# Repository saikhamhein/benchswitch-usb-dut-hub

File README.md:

# BenchSwitch USB DUT Hub

A four-port USB 2.0 DUT hub for embedded firmware development and automated hardware testing.

BenchSwitch was born from a practical need in agentic firmware development: let the development workflow power-cycle a device instead of waiting for someone to unplug it. The design combines a USB2514B hub controller with individually switched downstream power, targeting host control through tools such as `uhubctl`.

**Prototype: hardware testing is pending.** See the [build guide](doc/BUILD.md), [design constraints](doc/DESIGN_CONSTRAINTS.md) and [bring-up checklist](doc/BRINGUP.md) before building or powering a board.

## Hardware

- Four USB-A DUT ports and one USB-B upstream connection
- Per-port CH217A power switching and overcurrent signalling
- Regulated 12–24 V DC input with buck conversion
- Design targets: 1 A per port, 2 A shared DUT current
- 95 × 80 mm, four-layer PCB
- KiCad 10.0.6 sources; 131 fitted components across 41 catalog groups

## Build

Open [BenchSwitch_USB_DUT_Hub.kicad_pro](PCB/BenchSwitch_USB_DUT_Hub.kicad_pro) in KiCad 10.0.6.

- [Schematic](doc/PCB_Schematic_R5_LCSC.pdf) and [assembly drawing](doc/PCB_Assembly_R5_LCSC.pdf)
- [Gerber ZIP](manufacturing/R5_LCSC/DIN_USB_Hub_A8_R5_LCSC_Gerber.zip)
- [Exact component BOM](manufacturing/R5_LCSC/assembly/BOM_exact_per_reference.csv) and [per-board procurement list](manufacturing/R5_LCSC/LCSC_PROCUREMENT_PER_BOARD.csv)

With Python 3.9+, verify the release files or export to a new directory:

```sh
python manufacturing/tools/verify_release.py
python manufacturing/tools/export_manufacturing.py --output build/manufacturing
```

## Files

- `PCB/`: native design, symbols, footprints and models
- `manufacturing/`: fabrication files, BOM and build tools
- `doc/`: drawings, assembly guidance and test procedures

[CAD verification](doc/VERIFICATION.json) · [Third-party notices and optional model downloads](doc/THIRD_PARTY.md)

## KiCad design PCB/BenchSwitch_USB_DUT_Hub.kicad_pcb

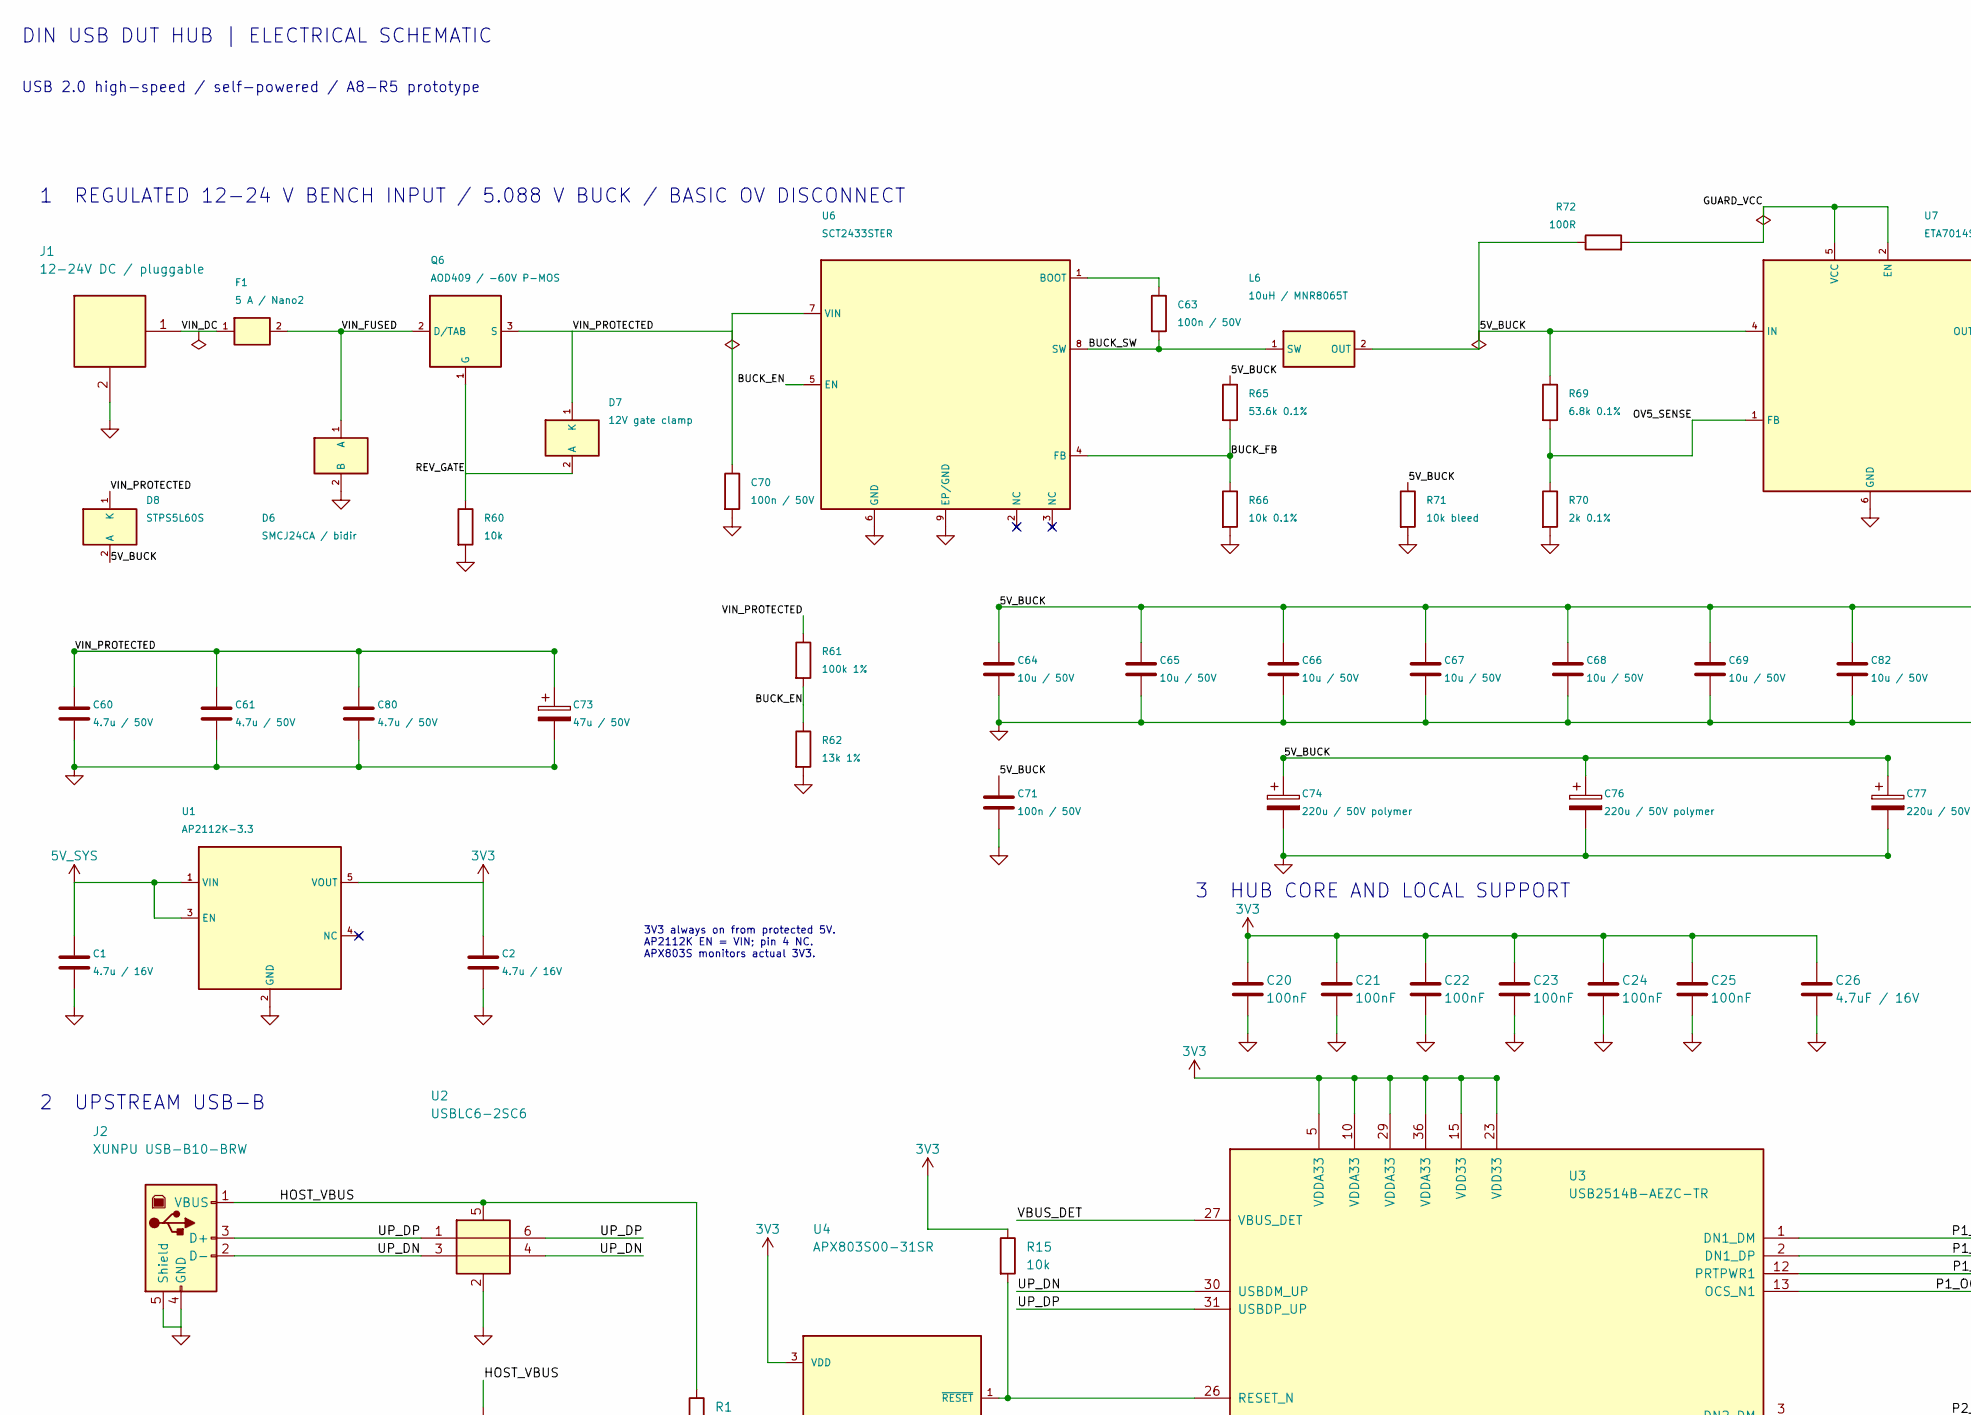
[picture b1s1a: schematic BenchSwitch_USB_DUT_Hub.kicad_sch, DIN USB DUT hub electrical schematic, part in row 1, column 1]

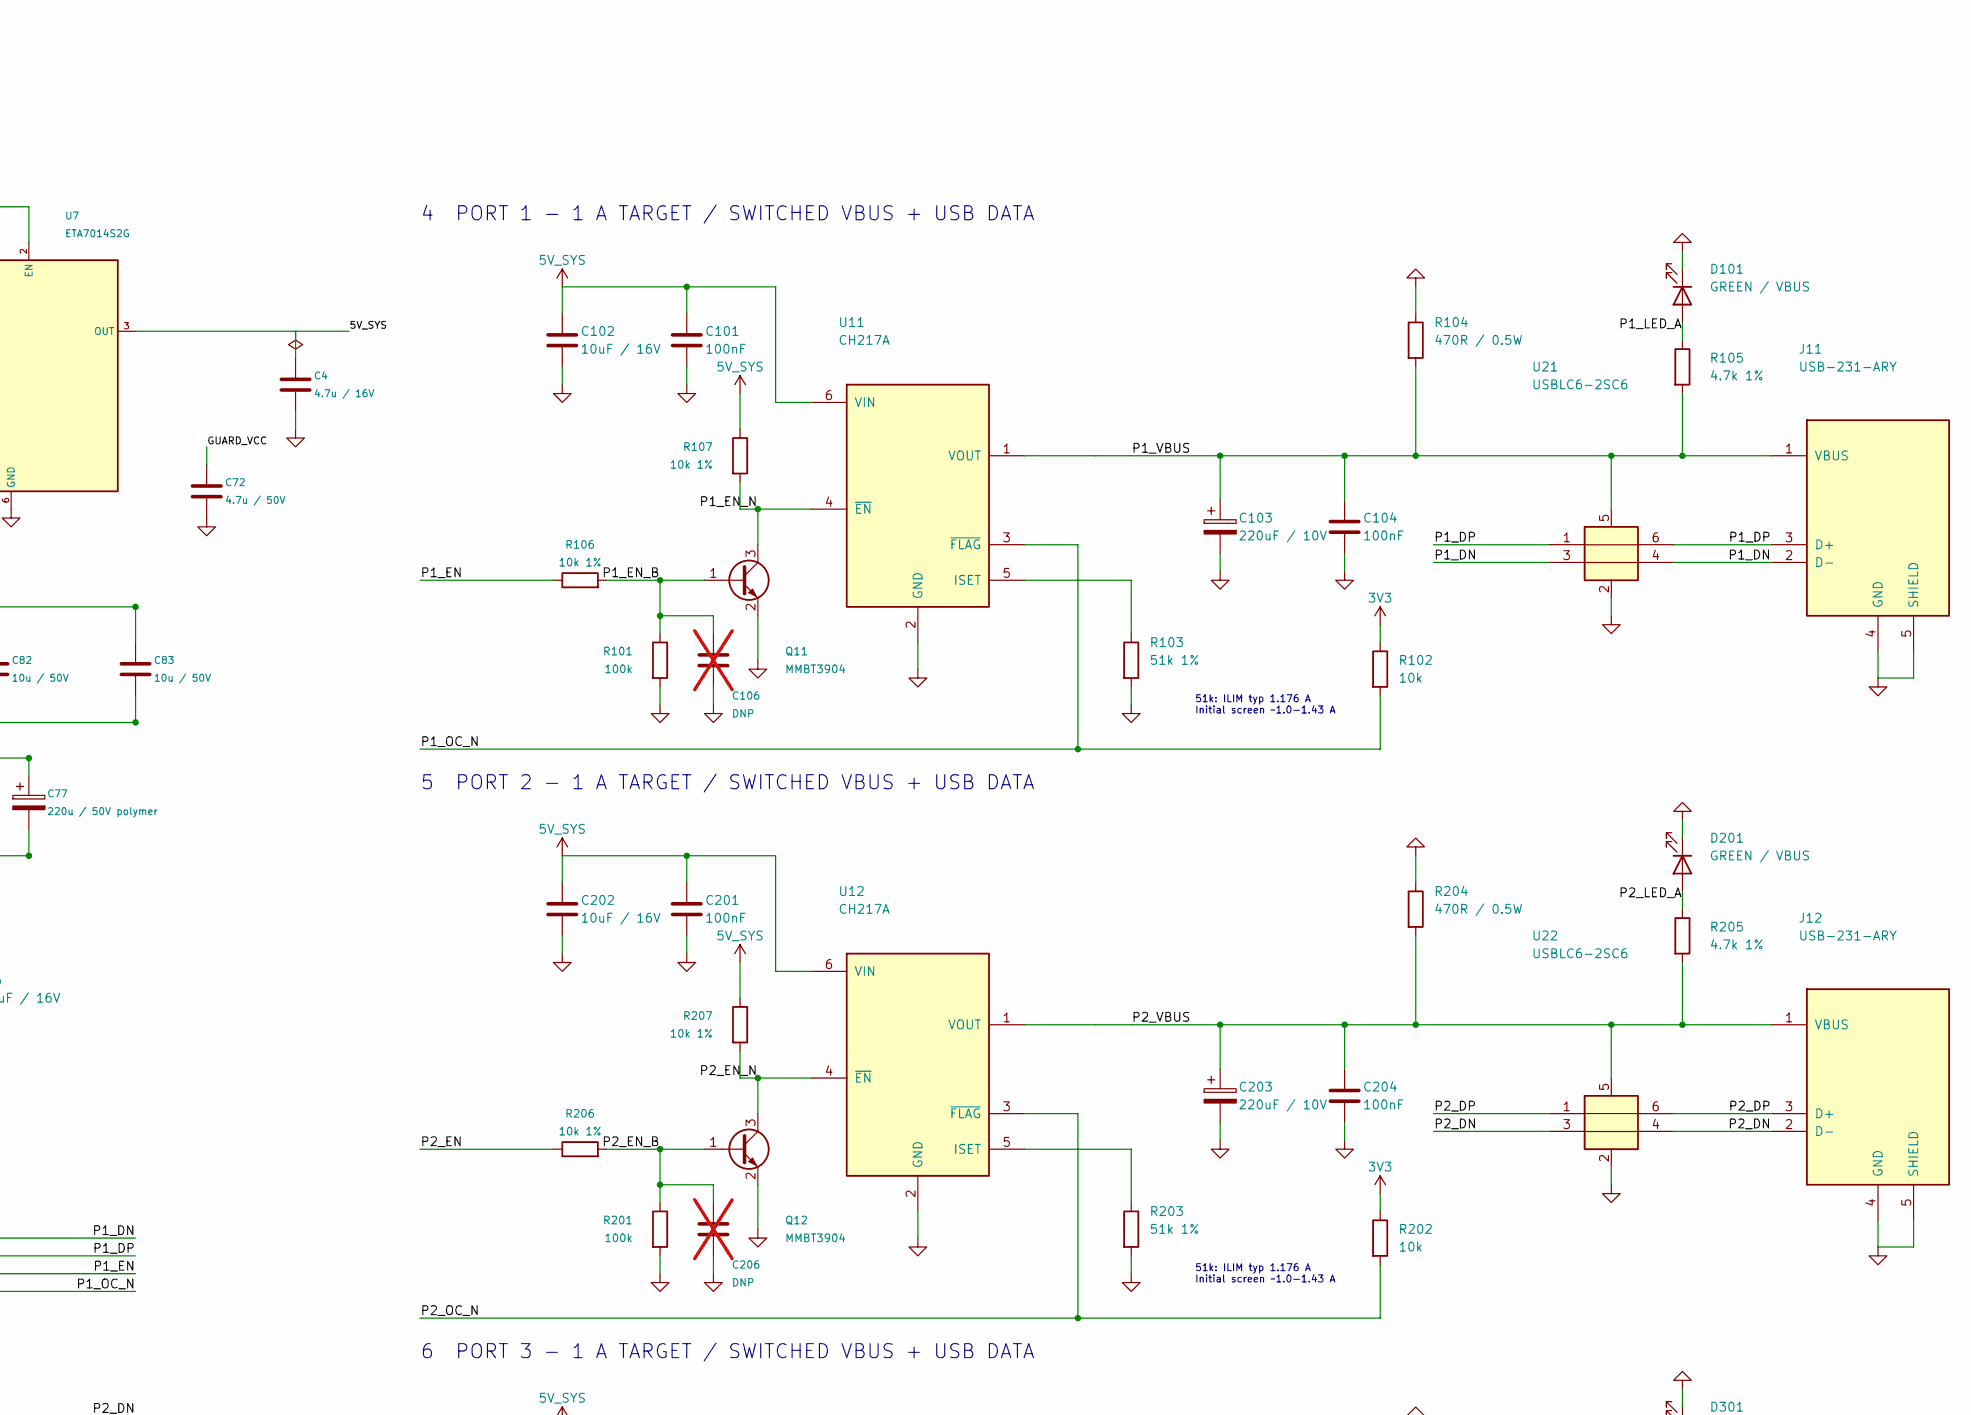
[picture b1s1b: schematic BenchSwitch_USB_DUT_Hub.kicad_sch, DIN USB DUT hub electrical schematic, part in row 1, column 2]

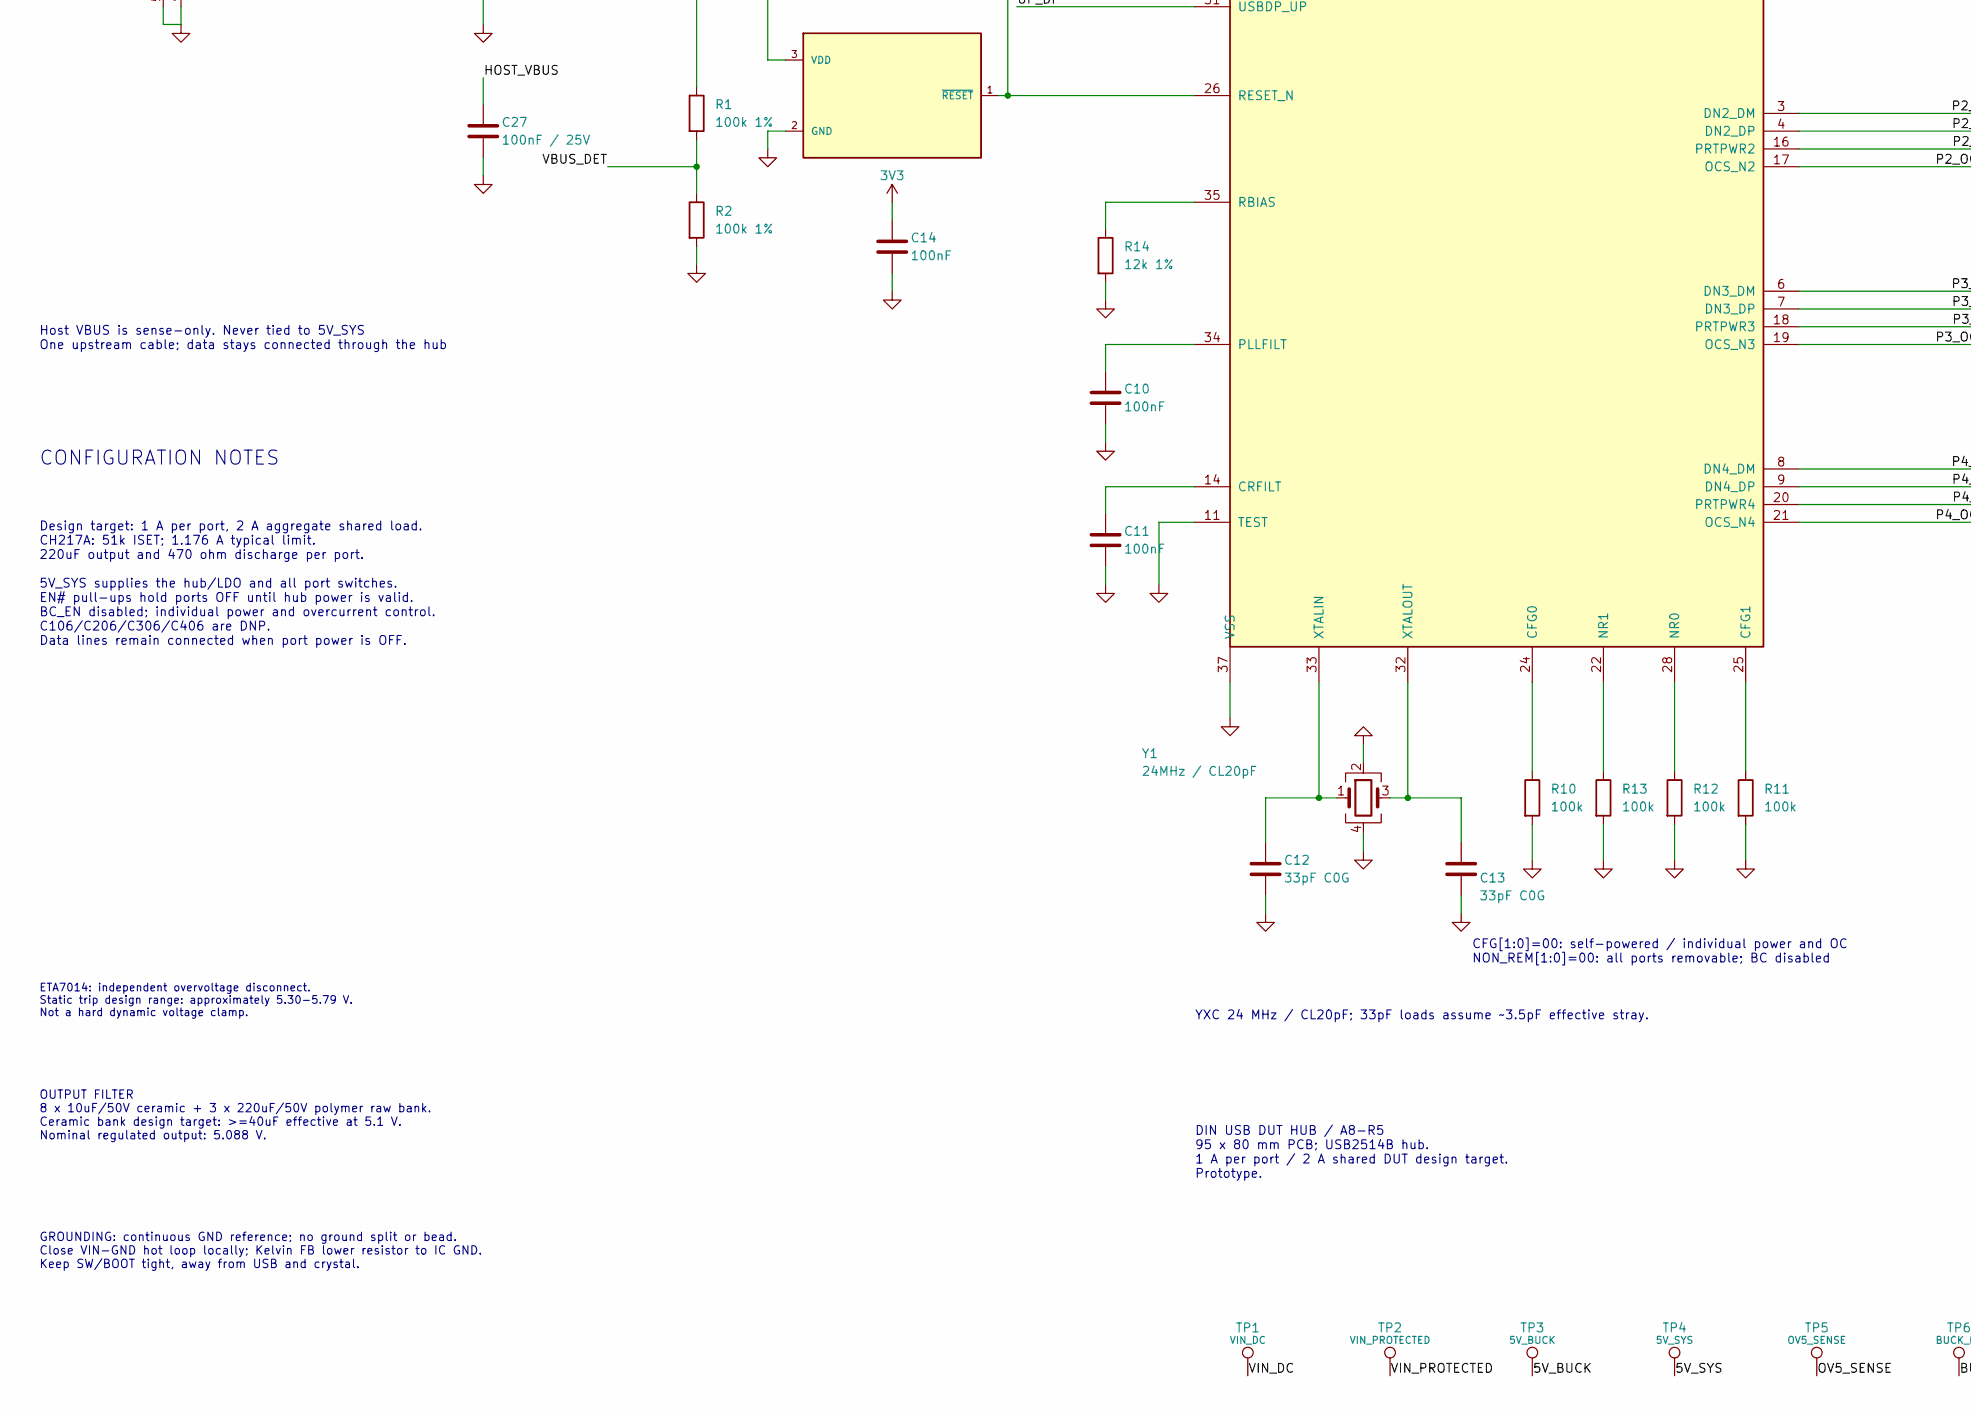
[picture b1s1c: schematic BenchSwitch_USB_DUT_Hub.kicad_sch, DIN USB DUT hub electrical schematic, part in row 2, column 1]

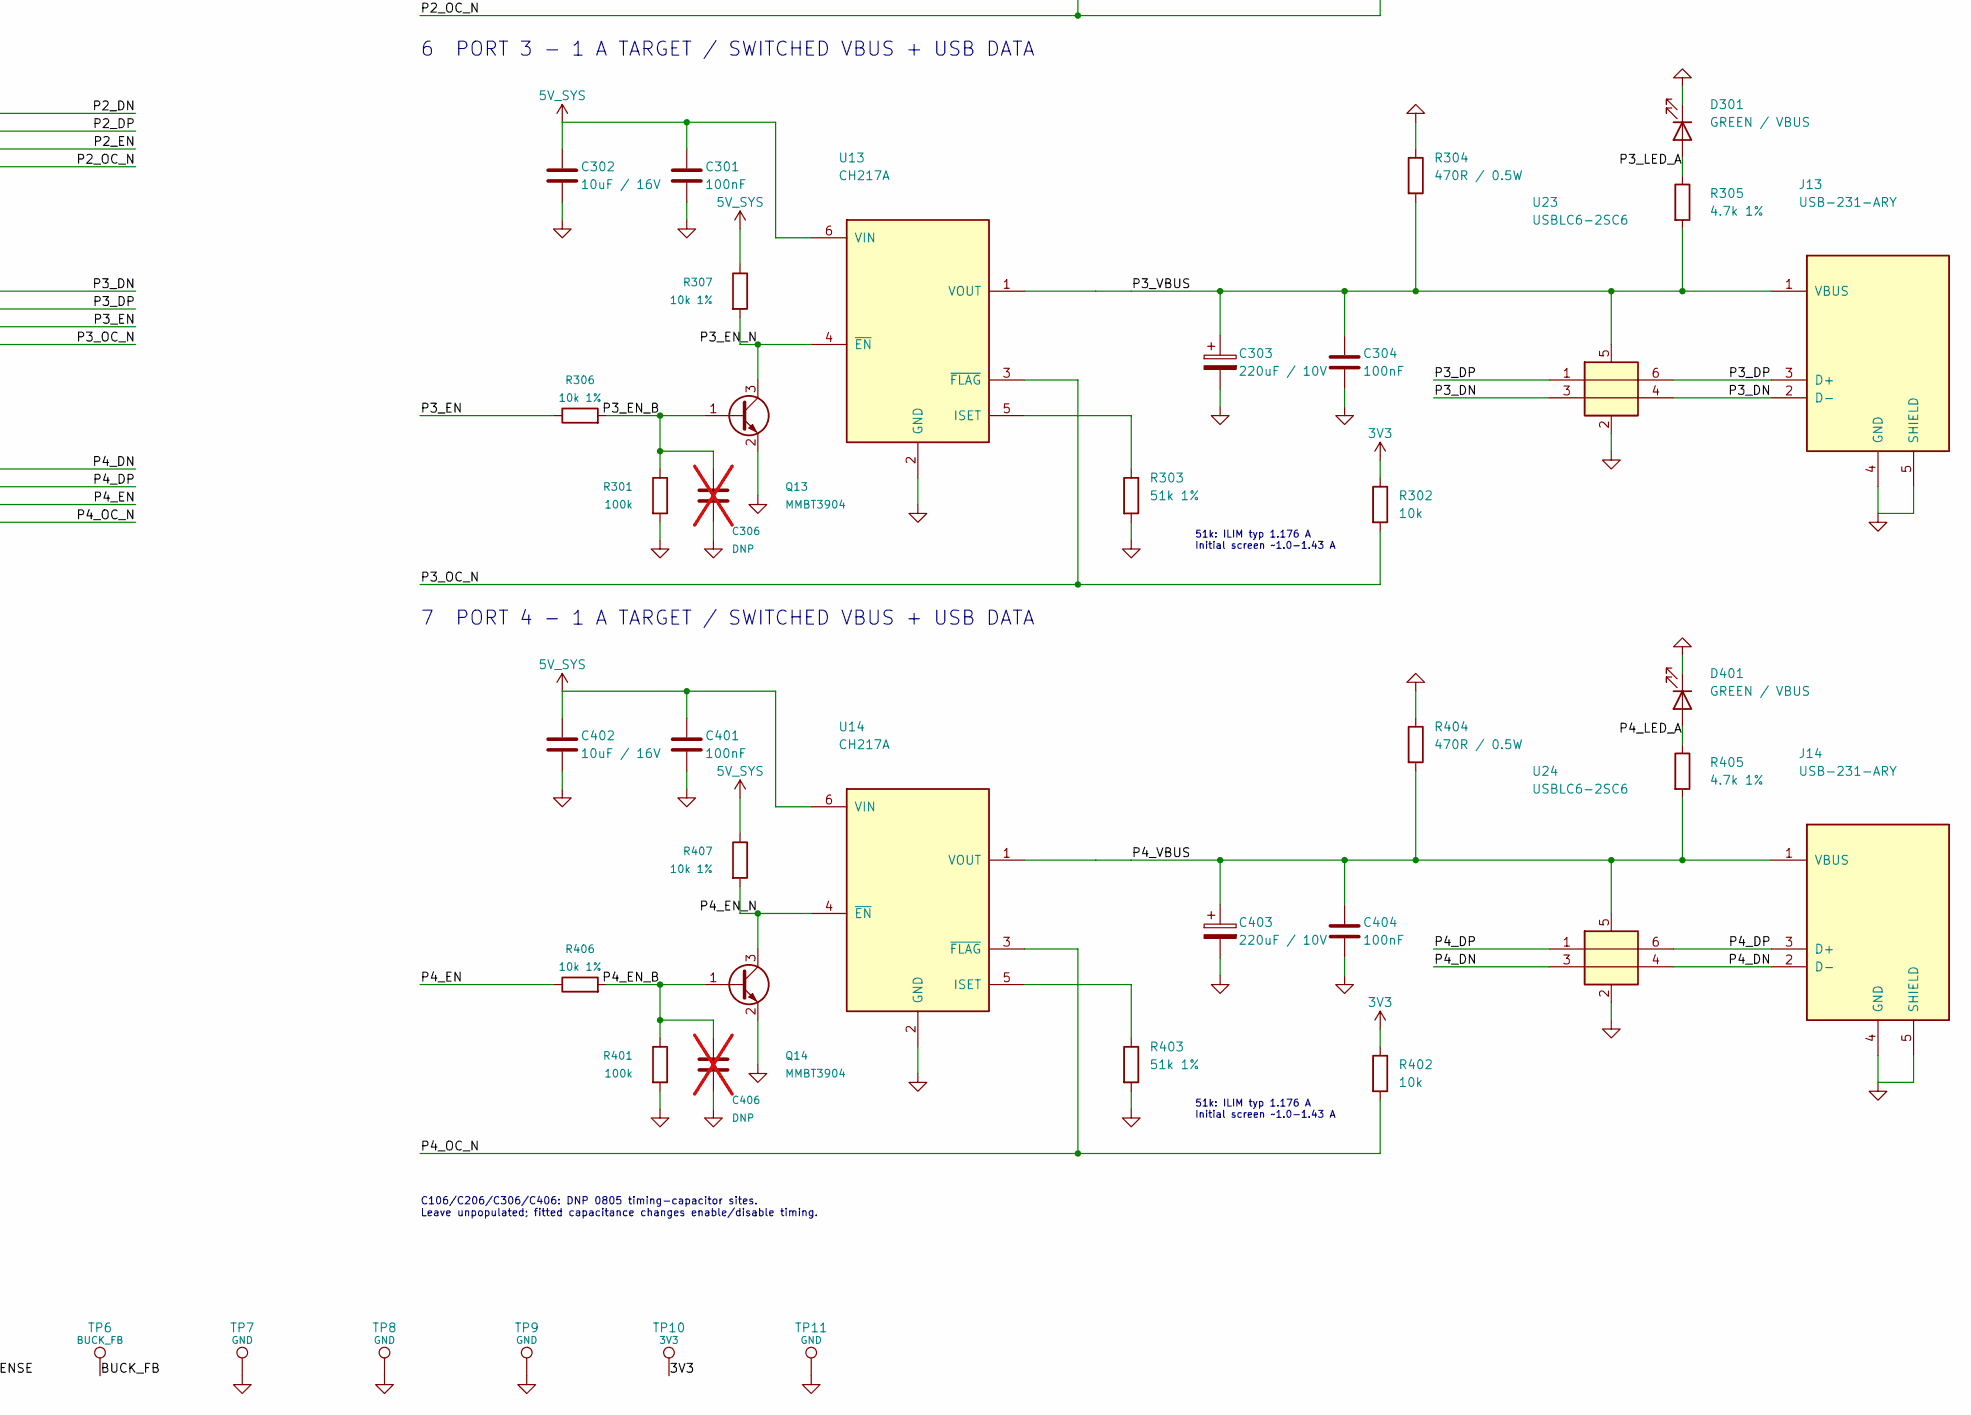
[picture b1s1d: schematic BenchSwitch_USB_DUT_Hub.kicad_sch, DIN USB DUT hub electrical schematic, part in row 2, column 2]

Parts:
C1, C2, C4: 4.7u / 16V; C_0805_2012Metric; MPN 0805B475K160NT; LCSC C880382
C10, C11, C14, C21, C22, C23, C24, C25, C101, C104, C201, C204, C301, C304, C401, C404: 100nF; C_0603_1608Metric; Tolerance 10%; MPN CC0603KRX7R9BB104; LCSC C14663
C12, C13: 33pF C0G; C_0603_1608Metric; MPN CL10C330JB8NNNC; LCSC C1663
C20: 100nF; C_0402_1005Metric; Tolerance 10%; MPN CC0402KRX7R8BB104; LCSC C105883
C26: 4.7uF / 16V; C_0805_2012Metric; MPN 0805B475K160NT; LCSC C880382
C27: 100nF / 25V; C_0402_1005Metric; Tolerance 10%; MPN CC0402KRX7R8BB104; LCSC C105883
C60, C61, C72, C80: 4.7u / 50V; C_1206_3216Metric; MPN 1206B475K500NT; LCSC C29823
C63, C70: 100n / 50V; R_0603_1608Metric; MPN CC0603KRX7R9BB104; LCSC C14663
C64, C65, C66, C67, C68, C69, C82, C83: 10u / 50V; Samsung_CL31_1206; MPN CL31B106KBHNFNE; LCSC C913957
C71: 100n / 50V; C_0603_1608Metric; MPN CC0603KRX7R9BB104; LCSC C14663
C73: 47u / 50V; CP_Radial_D6.3mm_P2.50mm; MPN SPZ1HM470E08O00RAXXX; LCSC C122243
C74, C76, C77: 220u / 50V polymer; CP_Radial_D10.0mm_P5.00mm; MPN SPZ1HM221G12O00RAXXX; LCSC C2691846
C102, C202, C302, C402: 10uF / 16V; C_0805_2012Metric; Tolerance 10%; MPN CC0805KKX7R7BB106; LCSC C326595
C103, C203, C303, C403: 220uF / 10V; CP_Radial_D6.3mm_P2.50mm; Tolerance 20%; MPN ERS1AM221E11OT; LCSC C106640
C106, C206, C306, C406: DNP; C_0805_2012Metric; not fitted
D6: SMCJ24CA / bidir; D_SMC; MPN SMCJ24CA-13-F; LCSC C135155
D7: 12V gate clamp; D_SOD-123F; MPN BZT52H-C12,115; LCSC C282531
D8: STPS5L60S; D_SMC; MPN STPS5L60S; LCSC C140620
D101, D201, D301, D401: GREEN / VBUS; LED_LiteOn_LTST-S270KGKT_SideView; MPN LTST-S270KGKT; LCSC C125113
F1: 5 A / Nano2; Fuse_Littelfuse-NANO2-451_453; MPN 0451005.MRL; LCSC C48467
J1: 12-24V DC / pluggable; Phoenix_MSTBA_1757242_2pos_P5.08; MPN 1757242; LCSC C90074
J2: XUNPU USB-B10-BRW; XUNPU_USB_B10_BRW; MPN USB-B10-BRW; LCSC C720549
J11, J12, J13, J14: USB-231-ARY; XUNPU_USB_231_ARY; MPN USB-231-ARY; LCSC C720525
L6: 10uH / MNR8065T; Sunlord_SWPA8065S; MPN MNR8065T100MT; LCSC C18222125
Q6: AOD409 / -60V P-MOS; AOS_AOD409_TO252; MPN AOD409; LCSC C36220
Q11, Q12, Q13, Q14: MMBT3904; SOT-23; MPN MMBT3904LT1G; LCSC C81464
R1, R2: 100k 1%; R_0603_1608Metric; Tolerance 1%; MPN 0603WAF1003T5E; LCSC C25803
R10, R11, R12, R13, R101, R201, R301, R401: 100k; R_0603_1608Metric; Tolerance 1%; MPN 0603WAF1003T5E; LCSC C25803
R14: 12k 1%; R_0603_1608Metric; Tolerance 1%; MPN 0603WAF1202T5E; LCSC C22790
R15, R102, R202, R302, R402: 10k; R_0603_1608Metric; Tolerance 1%; MPN RC0603FR-0710KL; LCSC C98220
R60: 10k; R_0603_1608Metric; MPN RC0603FR-0710KL; LCSC C98220
R61: 100k 1%; R_0603_1608Metric; MPN 0603WAF1003T5E; LCSC C25803
R62: 13k 1%; R_0603_1608Metric; MPN 0603WAF1302T5E; LCSC C22797
R65: 53.6k 0.1%; R_0603_1608Metric; MPN ERA-3AEB5362V; LCSC C2074540
R66: 10k 0.1%; R_0603_1608Metric; MPN RT0603BRD0710KL; LCSC C95204
R69: 6.8k 0.1%; R_0603_1608Metric; MPN RT0603BRD076K8L; LCSC C861539
R70: 2k 0.1%; R_0603_1608Metric; MPN PTFR0603B2K00P9; LCSC C328425
R71: 10k bleed; R_0603_1608Metric; MPN RC0603FR-0710KL; LCSC C98220
R72: 100R; R_0603_1608Metric; MPN 0603WAF1000T5E; LCSC C22775
R103, R203, R303, R403: 51k 1%; R_0603_1608Metric; MPN 0603WAF5102T5E; LCSC C23196
R104, R204, R304, R404: 470R / 0.5W; R_0805_2012Metric; Tolerance 1%; MPN ERJ-P06F4700V; LCSC C441978
R105, R205, R305, R405: 4.7k 1%; R_0603_1608Metric; MPN 0603WAF4701T5E; LCSC C23162
R106, R107, R206, R207, R306, R307, R406, R407: 10k 1%; R_0603_1608Metric; Tolerance 1%; MPN RC0603FR-0710KL; LCSC C98220
TP1: VIN_DC; Probe_1.0mm
TP2: VIN_PROTECTED; Probe_1.0mm
TP3: 5V_BUCK; Probe_1.0mm
TP4: 5V_SYS; Probe_1.0mm
TP5: OV5_SENSE; Probe_1.0mm
TP6: BUCK_FB; Probe_0.4mm
TP7, TP8, TP9, TP11: GND; Probe_1.0mm
TP10: 3V3; Probe_1.0mm
U1: AP2112K-3.3; SOT-23-5; MPN AP2112K-3.3TRG1; LCSC C51118
U2, U21, U22, U23, U24: USBLC6-2SC6; SOT-23-6; MPN USBLC6-2SC6; LCSC C7519
U3: USB2514B-AEZC-TR; QFN-36-1EP_6x6mm_P0.5mm_EP3.7x3.7mm; MPN USB2514B-AEZC-TR; LCSC C16251
U4: APX803S00-31SR; Diodes_APX803S_SR_SOT23; MPN APX803S00-31SR-7; LCSC C2067620
U6: SCT2433STER; SCT2433_ESOP8; MPN SCT2433STER; LCSC C509399
U7: ETA7014S2G; SOT-23-6; MPN ETA7014S2G; LCSC C7465500
U11, U12, U13, U14: CH217A; SOT-23-6; MPN CH217A; LCSC C54973763
Y1: 24MHz / CL20pF; YXC_YSX531SL_5032; Tolerance See exact manufacturer grade; MPN XL1EL89CSI-111YLC-24M; LCSC C18214302

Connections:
3V3: C2.1, C14.1, C20.1, C21.1, C22.1, C23.1, C24.1, C25.1, C26.1, R15.1, R102.1, R202.1, R302.1, R402.1, TP10.1, U1.5 (VOUT), U3.5 (VDDA33), U3.10 (VDDA33), U3.15 (VDD33), U3.23 (VDD33), U3.29 (VDDA33), U3.36 (VDDA33), U4.3 (VDD)
5V_SYS: C1.1, C4.1, C101.1, C102.1, C201.1, C202.1, C301.1, C302.1, C401.1, C402.1, R107.1, R207.1, R307.1, R407.1, TP4.1, U1.1 (VIN), U1.3 (EN), U7.3 (OUT), U11.6 (VIN), U12.6 (VIN), U13.6 (VIN), U14.6 (VIN)
/5V_BUCK: C64.1, C65.1, C66.1, C67.1, C68.1, C69.1, C71.1, C74.1, C76.1, C77.1, C82.1, C83.1, D8.2 (A), L6.2 (OUT), R65.1, R69.1, R71.1, R72.1, TP3.1, U7.4 (IN)
/BUCK_EN: R61.2, R62.1, U6.5 (EN)
/BUCK_FB: R65.2, R66.1, TP6.1, U6.4 (FB)
/BUCK_SW: C63.2, L6.1 (SW), U6.8 (SW)
/GUARD_VCC: C72.1, R72.2, U7.2 (EN), U7.5 (VCC)
/HOST_VBUS: C27.1, J2.1 (VBUS), R1.1, U2.5 (VBUS)
/OV5_SENSE: R69.2, R70.1, TP5.1, U7.1 (FB)
/P1_DN: J11.2 (D-), U3.1 (DN1_DM), U21.3 (I/O2), U21.4 (I/O2)
/P1_DP: J11.3 (D+), U3.2 (DN1_DP), U21.1 (I/O1), U21.6 (I/O1)
/P1_EN: R106.1, U3.12 (PRTPWR1)
/P1_EN_B: C106.1, Q11.1 (B), R101.1, R106.2
/P1_EN_N: Q11.3 (C), R107.2, U11.4 (~EN)
/P1_LED_A: D101.2 (A), R105.1
/P1_OC_N: R102.2, U3.13 (OCS_N1), U11.3 (~FLAG)
/P1_VBUS: C103.1, C104.1, J11.1 (VBUS), R104.2, R105.2, U11.1 (VOUT), U21.5 (VBUS)
/P2_DN: J12.2 (D-), U3.3 (DN2_DM), U22.3 (I/O2), U22.4 (I/O2)
/P2_DP: J12.3 (D+), U3.4 (DN2_DP), U22.1 (I/O1), U22.6 (I/O1)
/P2_EN: R206.1, U3.16 (PRTPWR2)
/P2_EN_B: C206.1, Q12.1 (B), R201.1, R206.2
/P2_EN_N: Q12.3 (C), R207.2, U12.4 (~EN)
/P2_LED_A: D201.2 (A), R205.1
/P2_OC_N: R202.2, U3.17 (OCS_N2), U12.3 (~FLAG)
/P2_VBUS: C203.1, C204.1, J12.1 (VBUS), R204.2, R205.2, U12.1 (VOUT), U22.5 (VBUS)
/P3_DN: J13.2 (D-), U3.6 (DN3_DM), U23.3 (I/O2), U23.4 (I/O2)
/P3_DP: J13.3 (D+), U3.7 (DN3_DP), U23.1 (I/O1), U23.6 (I/O1)
/P3_EN: R306.1, U3.18 (PRTPWR3)
/P3_EN_B: C306.1, Q13.1 (B), R301.1, R306.2
/P3_EN_N: Q13.3 (C), R307.2, U13.4 (~EN)
/P3_LED_A: D301.2 (A), R305.1
/P3_OC_N: R302.2, U3.19 (OCS_N3), U13.3 (~FLAG)
/P3_VBUS: C303.1, C304.1, J13.1 (VBUS), R304.2, R305.2, U13.1 (VOUT), U23.5 (VBUS)
/P4_DN: J14.2 (D-), U3.8 (DN4_DM), U24.3 (I/O2), U24.4 (I/O2)
/P4_DP: J14.3 (D+), U3.9 (DN4_DP), U24.1 (I/O1), U24.6 (I/O1)
/P4_EN: R406.1, U3.20 (PRTPWR4)
/P4_EN_B: C406.1, Q14.1 (B), R401.1, R406.2
/P4_EN_N: Q14.3 (C), R407.2, U14.4 (~EN)
/P4_LED_A: D401.2 (A), R405.1
/P4_OC_N: R402.2, U3.21 (OCS_N4), U14.3 (~FLAG)
/P4_VBUS: C403.1, C404.1, J14.1 (VBUS), R404.2, R405.2, U14.1 (VOUT), U24.5 (VBUS)
/REV_GATE: D7.2 (A), Q6.1 (G), R60.1
/UP_DN: J2.2 (D-), U2.3 (I/O2), U2.4 (I/O2), U3.30 (USBDM_UP)
/UP_DP: J2.3 (D+), U2.1 (I/O1), U2.6 (I/O1), U3.31 (USBDP_UP)
/VBUS_DET: R1.2, R2.1, U3.27 (VBUS_DET)
/VIN_DC: F1.1, J1.1 (VIN_DC), TP1.1
/VIN_FUSED: D6.1 (A), F1.2, Q6.2 (D/TAB)
/VIN_PROTECTED: C60.1, C61.1, C70.1, C73.1, C80.1, D7.1 (K), D8.1 (K), Q6.3 (S), R61.1, TP2.1, U6.7 (VIN)
GND: C1.2, C2.2, C4.2, C10.2, C11.2, C12.2, C13.2, C14.2, C20.2, C21.2, C22.2, C23.2, C24.2, C25.2, C26.2, C27.2, C60.2, C61.2, C64.2, C65.2, C66.2, C67.2, C68.2, C69.2, C70.2, C71.2, C72.2, C73.2, C74.2, C76.2, C77.2, C80.2, C82.2, C83.2, C101.2, C102.2, C103.2, C104.2, C106.2, C201.2, C202.2, C203.2, C204.2, C206.2, C301.2, C302.2, C303.2, C304.2, C306.2, C401.2, C402.2, C403.2, C404.2, C406.2, D6.2 (B), D101.1 (K), D201.1 (K), D301.1 (K), D401.1 (K), J1.2 (GND), J2.4 (GND), J2.5 (Shield), J11.4 (GND), J11.5 (SHIELD), J12.4 (GND), J12.5 (SHIELD), J13.4 (GND), J13.5 (SHIELD), J14.4 (GND), J14.5 (SHIELD), Q11.2 (E), Q12.2 (E), Q13.2 (E), Q14.2 (E), R2.2, R10.2, R11.2, R12.2, R13.2, R14.2, R60.2, R62.2, R66.2, R70.2, R71.2, R101.2, R103.2, R104.1, R201.2, R203.2, R204.1, R301.2, R303.2, R304.1, R401.2, R403.2, R404.1, TP7.1, TP8.1, TP9.1, TP11.1, U1.2 (GND), U2.2 (GND), U3.11 (TEST), U3.37 (VSS), U4.2 (GND), U6.6 (GND), U6.9 (EP/GND), U7.6 (GND), U11.2 (GND), U12.2 (GND), U13.2 (GND), U14.2 (GND), U21.2 (GND), U22.2 (GND), U23.2 (GND), U24.2 (GND), Y1.2, Y1.4
unnamed: R10.1, U3.24 (CFG0)
unnamed: R11.1, U3.25 (CFG1)
unnamed: C11.1, U3.14 (CRFILT)
unnamed: R12.1, U3.28 (NR0)
unnamed: R13.1, U3.22 (NR1)
unnamed: C10.1, U3.34 (PLLFILT)
unnamed: R14.1, U3.35 (RBIAS)
unnamed: R15.2, U3.26 (RESET_N), U4.1 (~RESET)
unnamed: C12.1, U3.33 (XTALIN), Y1.1
unnamed: C13.1, U3.32 (XTALOUT), Y1.3
unnamed: C63.1, U6.1 (BOOT)
unnamed: R103.1, U11.5 (ISET)
unnamed: R203.1, U12.5 (ISET)
unnamed: R303.1, U13.5 (ISET)
unnamed: R403.1, U14.5 (ISET)

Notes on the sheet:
DIN USB DUT HUB | ELECTRICAL SCHEMATIC
USB 2.0 high-speed / self-powered / A8-R5 prototype
1 REGULATED 12-24 V BENCH INPUT / 5.088 V BUCK / BASIC OV DISCONNECT
2 UPSTREAM USB-B
Host VBUS is sense-only. Never tied to 5V_SYS One upstream cable; data stays connected through the hub
3 HUB CORE AND LOCAL SUPPORT
CFG[1:0]=00: self-powered / individual power and OC NON_REM[1:0]=00: all ports removable; BC disabled
4 PORT 1 - 1 A TARGET / SWITCHED VBUS + USB DATA
5 PORT 2 - 1 A TARGET / SWITCHED VBUS + USB DATA
6 PORT 3 - 1 A TARGET / SWITCHED VBUS + USB DATA
7 PORT 4 - 1 A TARGET / SWITCHED VBUS + USB DATA
CONFIGURATION NOTES
Design target: 1 A per port, 2 A aggregate shared load. CH217A: 51k ISET; 1.176 A typical limit. 220uF output and 470 ohm discharge per port. 5V_SYS supplies the hub/LDO and all port switches. EN# pull-ups hold ports OFF until hub power is valid. BC_EN disabled; individual power and overcurrent con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
DIN USB DUT HUB / A8-R5 95 x 80 mm PCB; USB2514B hub. 1 A per port / 2 A shared DUT design target. Prototype.
YXC 24 MHz / CL20pF; 33pF loads assume ~3.5pF effective stray.
ETA7014: independent overvoltage disconnect. Static trip design range: approximately 5.30-5.79 V. Not a hard dynamic voltage clamp.
OUTPUT FILTER 8 x 10uF/50V ceramic + 3 x 220uF/50V polymer raw bank. Ceramic bank design target: >=40uF effective at 5.1 V. Nominal regulated output: 5.088 V.
GROUNDING: continuous GND reference; no ground split or bead. Close VIN-GND hot loop locally; Kelvin FB lower resistor to IC GND. Keep SW/BOOT tight, away from USB and crystal.
51k: ILIM typ 1.176 A Initial screen ~1.0-1.43 A
C106/C206/C306/C406: DNP 0805 timing-capacitor sites. Leave unpopulated; fitted capacitance changes enable/disable timing.
3V3 always on from protected 5V. AP2112K EN = VIN; pin 4 NC. APX803S monitors actual 3V3.

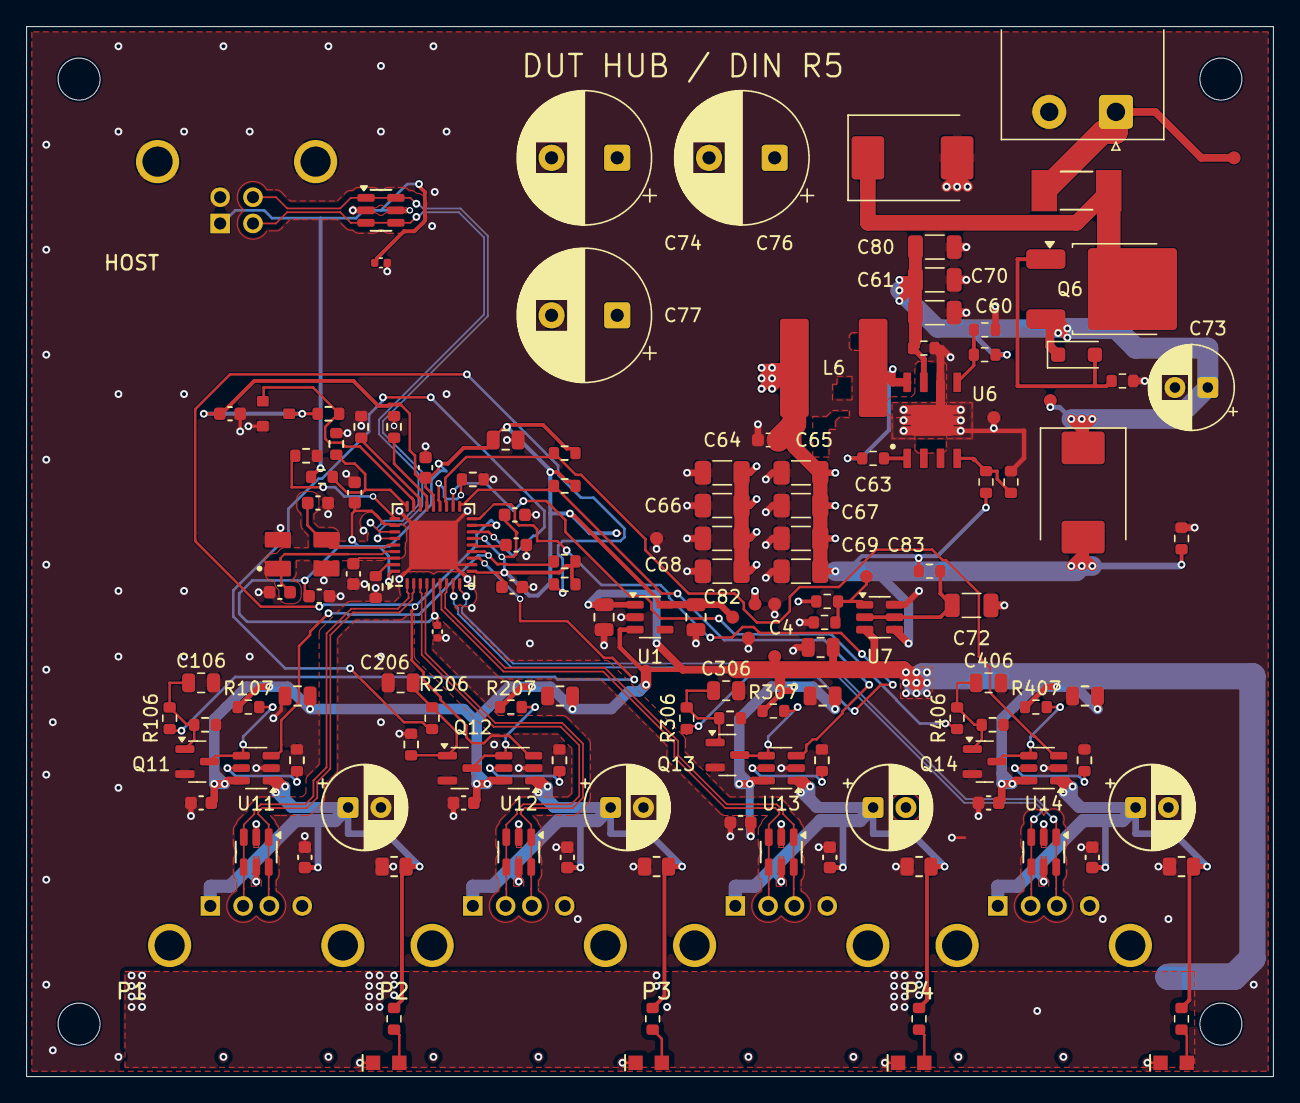
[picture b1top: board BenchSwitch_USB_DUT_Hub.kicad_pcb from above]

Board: 4 copper layers, 95.0 x 80.0 mm, 150 parts (0 on the bottom side), 64 nets.

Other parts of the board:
H1, H2, H3, H4: M3 / 3.2mm NPTH; MountingHole_3.2mm_Enclosure_Post
